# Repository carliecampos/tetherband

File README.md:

# tetherband
Tetherband Board and Schematic Files 

All CAD files and libraries were created using EAGLE CAD. 

The Tetherband repository includes the board and schematic files for: 

A. PC-003 
   This is the prototyping board and has an arduino style pin header for analog control of each subsystem. There is no MCU included. 
B. PC-004
   This is the first completed board and includes the BM832 MCU and a JTAG connector for uploading firmware. The power button was not populated during testing. 
C. Tesseract Library
   This is the library used for all componenets added to PC-003 and PC-003 that were not included in the standard component libraries.

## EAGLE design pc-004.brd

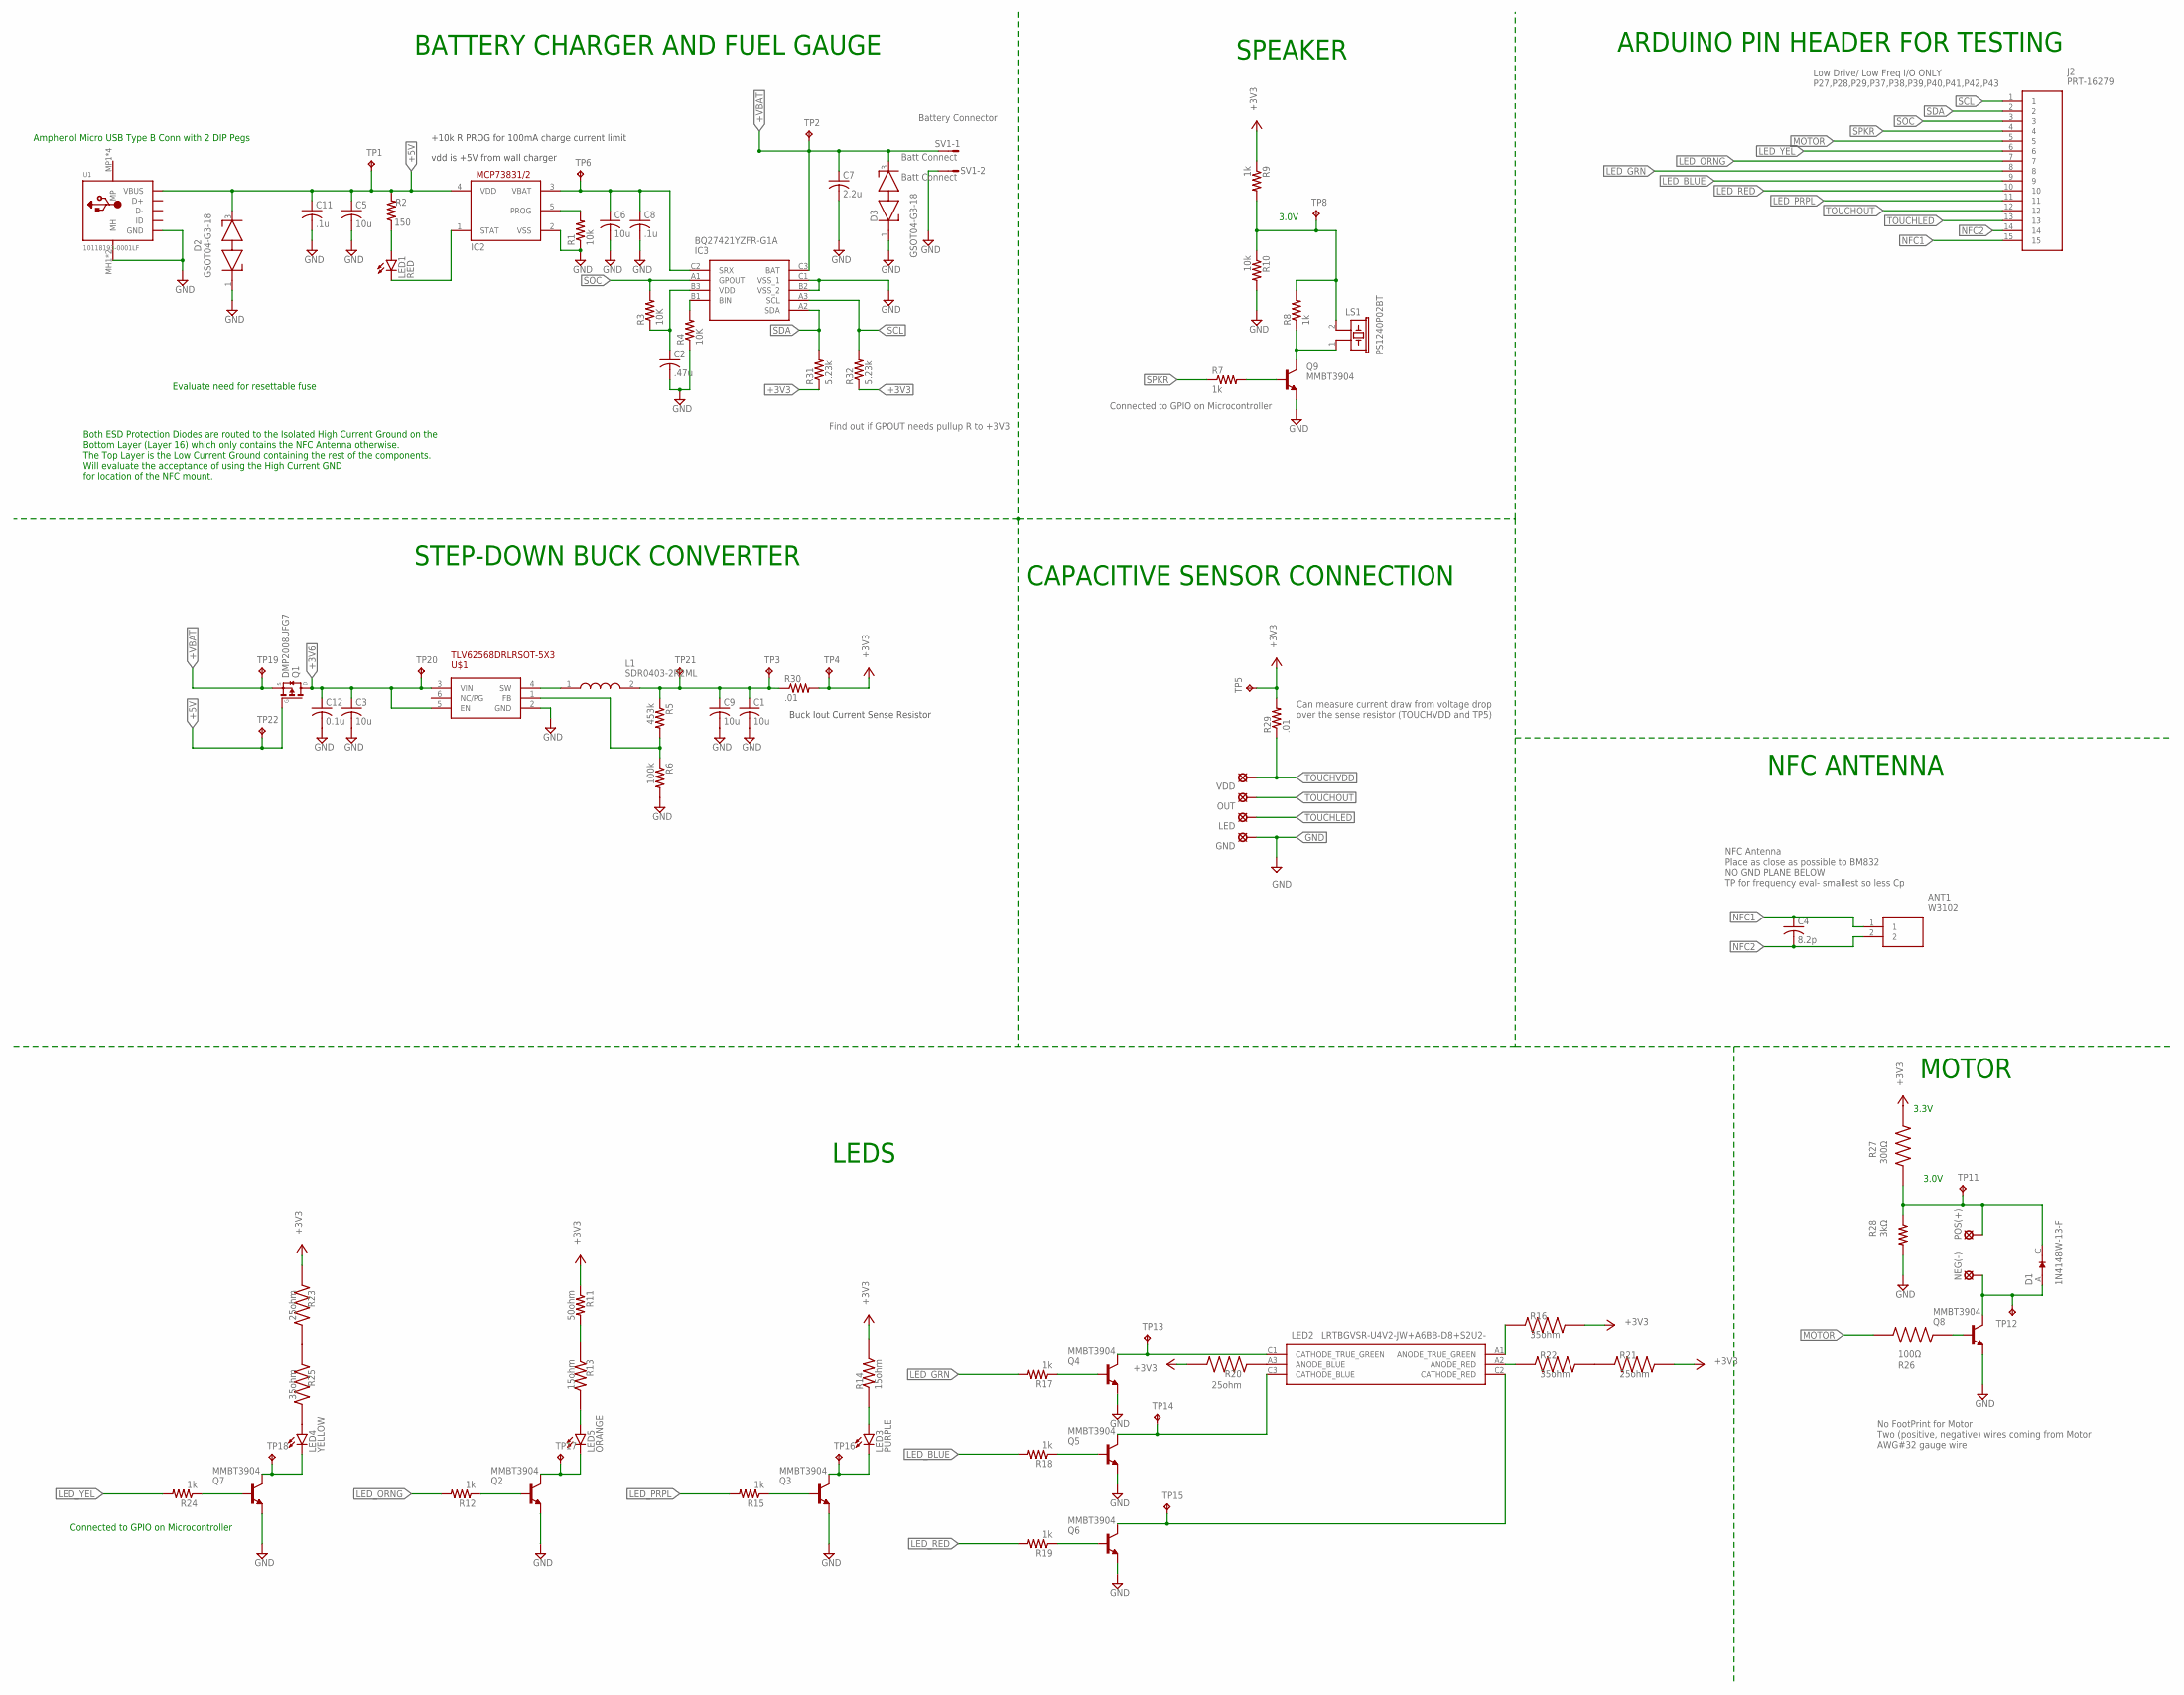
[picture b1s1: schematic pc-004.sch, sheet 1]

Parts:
ANT1: W3102
C1, C3, C5, C6, C9: 10u; CAPC2012X140N
C2: .47u; C0603
C4: 8.2p; C0402K
C7: 2.2u; C0603
C8, C11: .1u; C0603
C12: 0.1u; C0603
D1: 1N4148W-13-F; SOD3715X135N
D2, D3: GSOT04-G3-18; SOT23
GND: LSP10
IC2: MCP73831/OT; SOT23-5L
IC3: BQ27421YZFR-G1A; BGA9C50P3X3_158X162X62
J2: PRT-16279; PRT16279
L1: SDR0403-2R2ML; SDR04032R2ML
LED: LSP10
LED1: RED; LEDC1608X80N
LED2: LRTBGVSR-U4V2-JW+A6BB-D8+S2U2-; LRTBGVSRU4V2JWA6BBD8S2U27Z20S
LED3: PURPLE; LEDC3216X125N
LED4: YELLOW; SML0603
LED5: ORANGE; SML0603
LS1: PS1240P02BT
NEG(-): LSP10
OUT: LSP10
POS(+): LSP10
Q1: DMP2008UFG7
Q2, Q3, Q4, Q5, Q6, Q7, Q8, Q9: MMBT3904; SOT23
R1, R10: 10k; R0402
R2: 150; R0402
R3, R4: 10K; R0402
R5: 453k; R0402
R6: 100k; R0603
R7, R8, R9, R12, R15, R17, R18, R19, R24: 1k; RESC1608X55N
R11: 50ohm; RESC1005X35N
R13, R14: 15ohm; RESC1608X55N
R16, R22, R25: 35ohm; RESC1608X55N
R20, R21, R23: 25ohm; RESC2012X65N
R26: 100Ω; RESC1608X55N
R27: 300Ω; RESC3015X65N
R28: 3kΩ; RESC3216X75N
R29: .01; R0603
R30: .01; RESC3216X68N
R31, R32: 5.23k; R0603
SV1: Batt Connect; L02P
TP1, TP2, TP3, TP4, TP5, TP6, TP8, TP11, TP12, TP13, TP14, TP15, TP16, TP17, TP18, TP19, TP20, TP21, TP22: TESTPOINT; TESTPOINT_PAD-036
U1: 10118193-0001LF; 101181930001LF
U$1: TLV62568DRLRSOT-5X3; SOT50P160X60-6N
VDD: LSP10

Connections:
+3V3: R9.1, R11.1, R14.2, R16.2, R20.2, R21.2, R23.1, R27.1, R29.2, R30.2, R31.1, R32.1, TP4.1, TP5.1; also elsewhere on the board
+3V6: C3.1, C12.1, Q1.5 (D), Q1.6 (D), Q1.7 (D), Q1.8 (D), Q1.9 (D), TP20.1, U$1.3 (VIN), U$1.5 (EN)
+5V: C5.1, C11.1, D2.3 (K2), IC2.4 (VDD), Q1.4 (G), R2.2, TP1.1, TP22.1, U1.1 (VBUS)
+VBAT: C7.1, D3.3 (K2), IC3.C3 (BAT), Q1.1 (S), Q1.2 (S), Q1.3 (S), SV1.1, TP2.1, TP19.1
GND: C1.2, C2.2, C3.2, C5.2, C6.2, C7.2, C8.2, C9.2, C11.2, C12.2, D2.1 (K1), D3.1 (K1), GND.MP, IC2.2 (VSS), IC3.B2 (VSS_2), IC3.C1 (VSS_1), Q2.2 (E), Q3.2 (E), Q4.2 (E), Q5.2 (E), Q6.2 (E), Q7.2 (E), Q8.2 (E), Q9.2 (E), R1.1, R4.1, R6.2, R10.2, R28.2, SV1.2, U1.5 (GND), U1.MH1 (MH), U1.MH2 (MH), U$1.2 (GND); also elsewhere on the board
LED_BLUE: J2.9, R18.2; also elsewhere on the board
LED_GRN: J2.8, R17.2; also elsewhere on the board
LED_ORNG: J2.7, R12.2; also elsewhere on the board
LED_PRPL: J2.11, R15.2; also elsewhere on the board
LED_RED: J2.10, R19.2; also elsewhere on the board
LED_YEL: J2.6, R24.2; also elsewhere on the board
MOTOR: J2.5, R26.1; also elsewhere on the board
unnamed: Q9.1 (B), R7.2
unnamed: LS1.1, Q9.3 (C), R8.1
unnamed: IC2.5 (PROG), R1.2
unnamed: L1.1, U$1.4 (SW)
unnamed: R5.2, R6.1, U$1.1 (FB)
unnamed: IC2.1 (STAT), LED1.1 (C)
unnamed: LED1.2 (A), R2.1
unnamed: Q8.1 (B), R26.2
unnamed: IC3.B1 (BIN), R4.2
unnamed: LS1.2, R8.2, R9.2, R10.1, TP8.1
unnamed: D1.C (K), POS(+).MP, R27.2, R28.1, TP11.1
unnamed: Q2.1 (B), R12.1
unnamed: LED5.C, Q2.3 (C), TP17.1
unnamed: R11.2, R13.1
unnamed: LED5.A, R13.2
unnamed: C1.1, C9.1, L1.2, R5.1, R30.1, TP3.1, TP21.1
unnamed: Q3.1 (B), R15.1
unnamed: LED3.1 (C), Q3.3 (C), TP16.1
unnamed: LED3.2 (A), R14.1
unnamed: R21.1, R22.2
unnamed: Q4.1 (B), R17.1
unnamed: LED2.C1 (CATHODE_TRUE_GREEN), Q4.3 (C), TP13.1
unnamed: D1.A, NEG(-).MP, Q8.3 (C), TP12.1
unnamed: Q5.1 (B), R18.1
unnamed: C6.1, C8.1, IC2.3 (VBAT), IC3.C2 (SRX), TP6.1
unnamed: Q6.1 (B), R19.1
unnamed: LED2.C3 (CATHODE_BLUE), Q5.3 (C), TP14.1
unnamed: LED2.A3 (ANODE_BLUE), R20.1
unnamed: LED2.A1 (ANODE_TRUE_GREEN), R16.1
unnamed: LED2.C2 (CATHODE_RED), Q6.3 (C), TP15.1
unnamed: LED2.A2 (ANODE_RED), R22.1
unnamed: Q7.1 (B), R24.1
unnamed: LED4.C, Q7.3 (C), TP18.1
unnamed: LED4.A, R25.2
unnamed: R23.2, R25.1
unnamed: C2.1, IC3.B3 (VDD), R3.1
NFC1: ANT1.1, C4.1, J2.15; also elsewhere on the board
NFC2: ANT1.2, C4.2, J2.14; also elsewhere on the board
SCL: IC3.A3 (SCL), J2.1, R32.2; also elsewhere on the board
SDA: IC3.A2 (SDA), J2.2, R31.2; also elsewhere on the board
SOC: IC3.A1 (GPOUT), J2.3, R3.2; also elsewhere on the board
SPKR: J2.4, R7.1; also elsewhere on the board
TOUCHLED: J2.13, LED.MP
TOUCHOUT: J2.12, OUT.MP; also elsewhere on the board
TOUCHVDD: R29.1, VDD.MP

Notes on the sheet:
NFC Antenna Place as close as possible to BM832 NO GND PLANE BELOW TP for frequency eval- smallest so less Cp
vdd is +5V from wall charger
+10k R PROG for 100mA charge current limit
Battery Connector
Low Drive/ Low Freq I/O ONLY P27,P28,P29,P37,P38,P39,P40,P41,P42,P43
Connected to GPIO on Microcontroller
3.0V
3.3V
No FootPrint for Motor Two (positive, negative) wires coming from Motor AWG#32 gauge wire
Evaluate need for resettable fuse
Buck Iout Current Sense Resistor
NFC ANTENNA
CAPACITIVE SENSOR CONNECTION
SPEAKER
BATTERY CHARGER AND FUEL GAUGE
STEP-DOWN BUCK CONVERTER
LEDS
MOTOR
ARDUINO PIN HEADER FOR TESTING
Find out if GPOUT needs pullup R to +3V3
Can measure current draw from voltage drop over the sense resistor (TOUCHVDD and TP5)
Amphenol Micro USB Type B Conn with 2 DIP Pegs
Both ESD Protection Diodes are routed to the Isolated High Current Ground on the Bottom Layer (Layer 16) which only contains the NFC Antenna otherwise. The Top Layer is the Low Current Ground containing the rest of the components. Will evaluate the acceptance of using the High Current GND for locat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

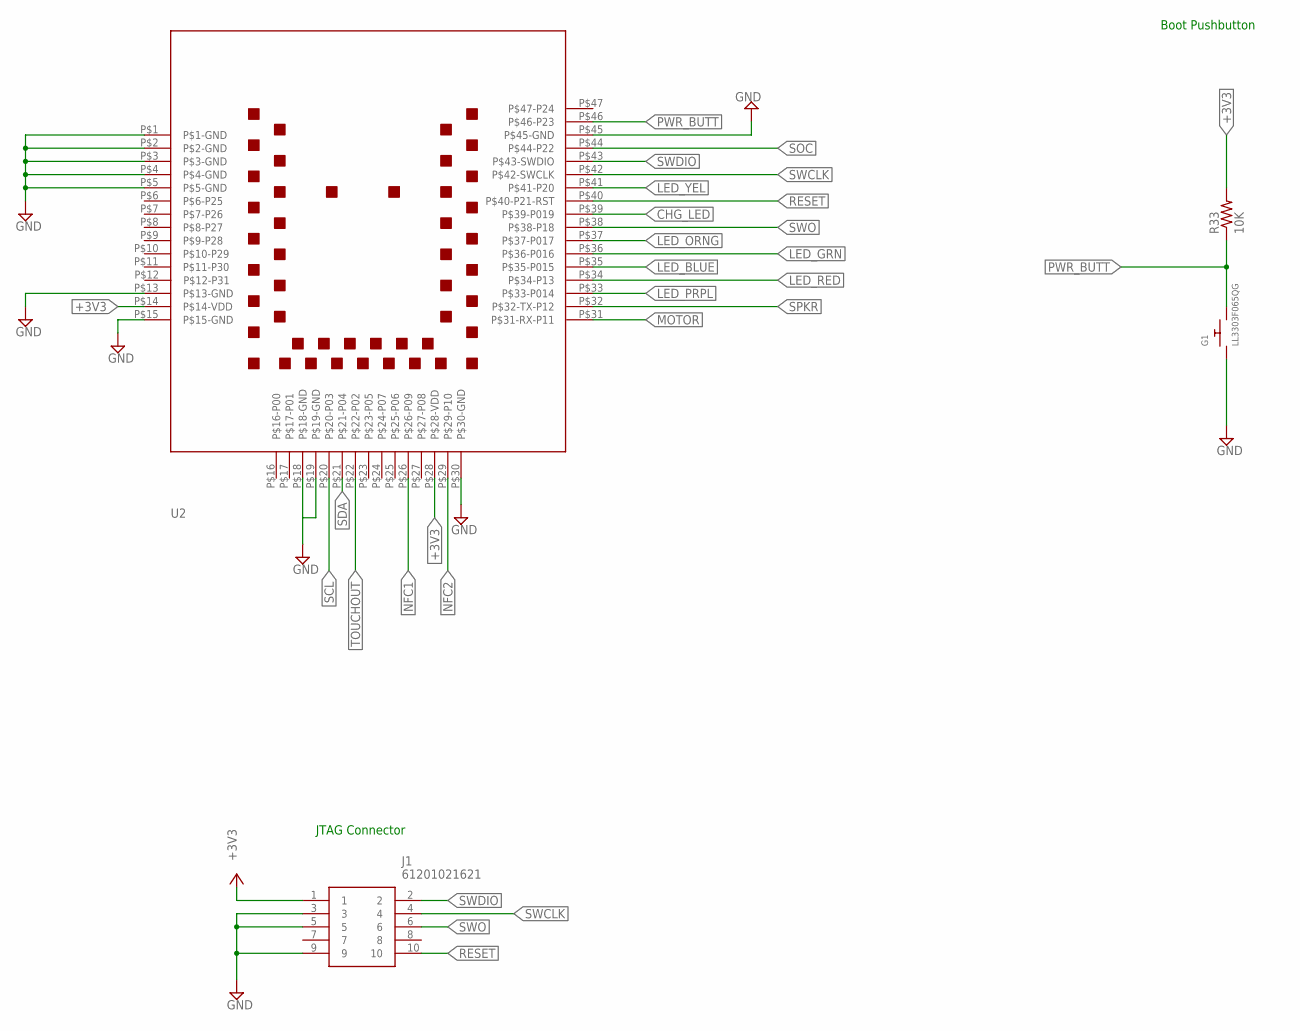
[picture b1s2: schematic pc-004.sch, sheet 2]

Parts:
G1: LL3303F065QG
J1: 61201021621; SHDR10W64P254_2X5_2036X885X925
R33: 10K; R0402
U2: BM832

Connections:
+3V3: J1.1, R33.2, U2.P$14 (P$14-VDD), U2.P$28 (P$28-VDD); also elsewhere on the board
CHG_LED: U2.P$39 (P$39-P019)
GND: G1.P$1, G1.P$2, J1.3, J1.5, J1.9, U2.P$1 (P$1-GND), U2.P$2 (P$2-GND), U2.P$3 (P$3-GND), U2.P$4 (P$4-GND), U2.P$5 (P$5-GND), U2.P$13 (P$13-GND), U2.P$15 (P$15-GND), U2.P$18 (P$18-GND), U2.P$19 (P$19-GND), U2.P$30 (P$30-GND), U2.P$45 (P$45-GND); also elsewhere on the board
LED_BLUE: U2.P$35 (P$35-P015); also elsewhere on the board
LED_GRN: U2.P$36 (P$36-P016); also elsewhere on the board
LED_ORNG: U2.P$37 (P$37-P017); also elsewhere on the board
LED_PRPL: U2.P$33 (P$33-P014); also elsewhere on the board
LED_RED: U2.P$34 (P$34-P13); also elsewhere on the board
LED_YEL: U2.P$41 (P$41-P20); also elsewhere on the board
MOTOR: U2.P$31 (P$31-RX-P11); also elsewhere on the board
NFC1: U2.P$26 (P$26-P09); also elsewhere on the board
NFC2: U2.P$29 (P$29-P10); also elsewhere on the board
PWR_BUTT: G1.P$3, G1.P$4, R33.1, U2.P$46 (P$46-P23)
RESET: J1.10, U2.P$40 (P$40-P21-RST)
SCL: U2.P$20 (P$20-P03); also elsewhere on the board
SDA: U2.P$21 (P$21-P04); also elsewhere on the board
SOC: U2.P$44 (P$44-P22); also elsewhere on the board
SPKR: U2.P$32 (P$32-TX-P12); also elsewhere on the board
SWCLK: J1.4, U2.P$42 (P$42-SWCLK)
SWDIO: J1.2, U2.P$43 (P$43-SWDIO)
SWO: J1.6, U2.P$38 (P$38-P18)
TOUCHOUT: U2.P$22 (P$22-P02); also elsewhere on the board

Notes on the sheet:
Boot Pushbutton
JTAG Connector

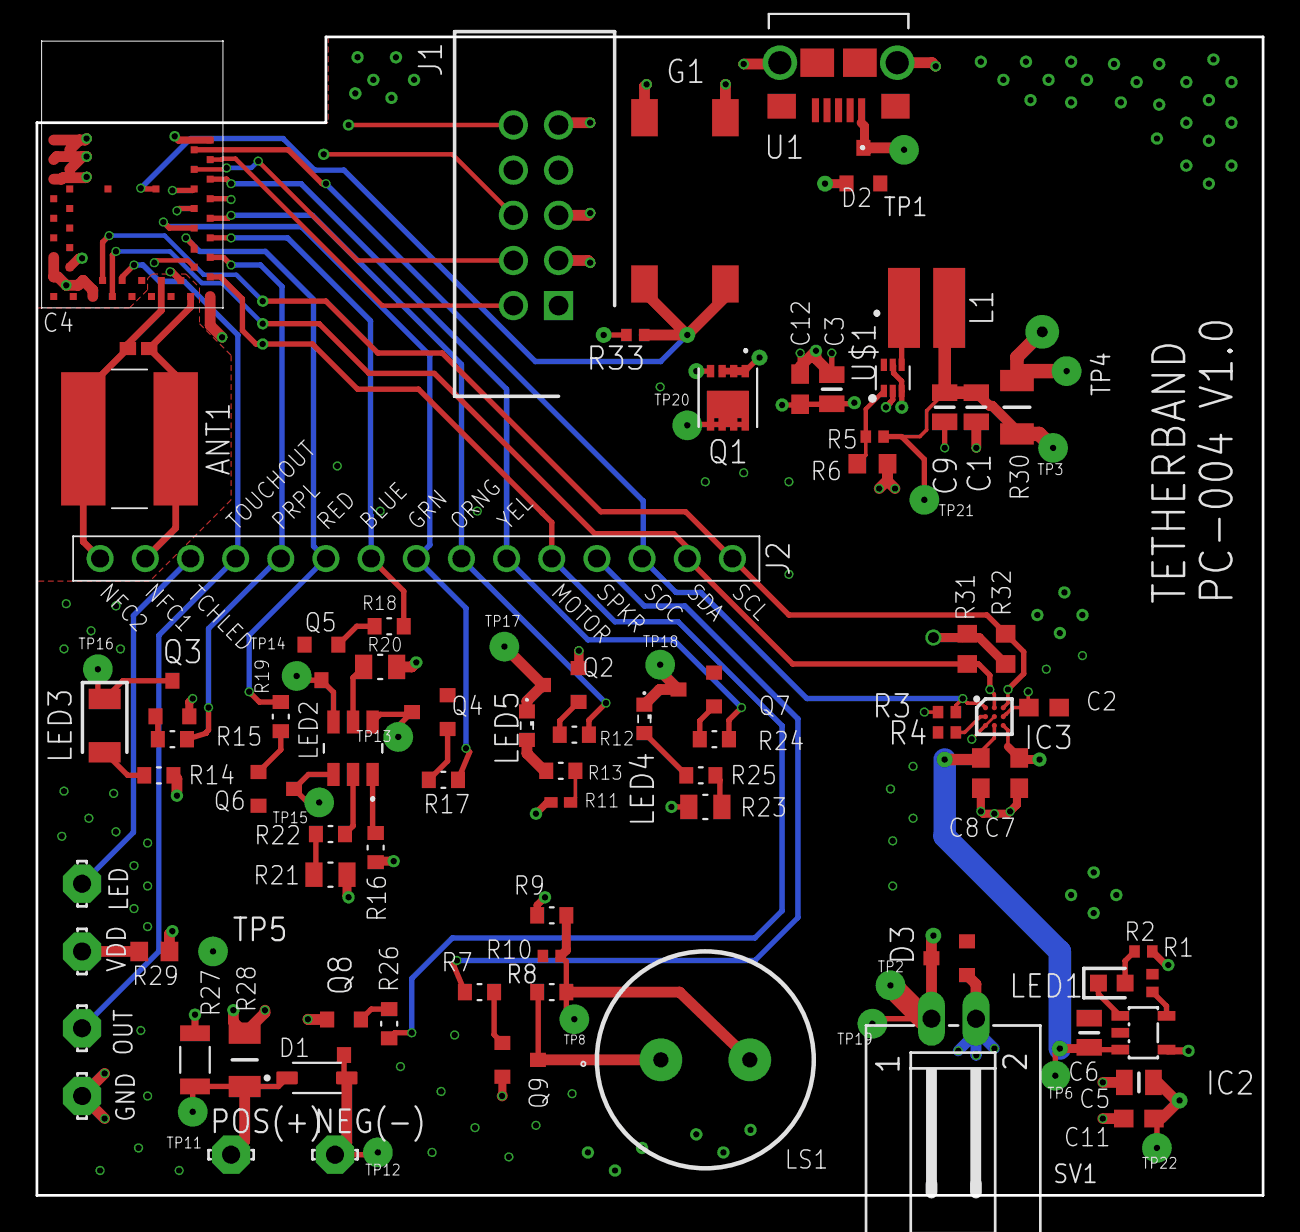
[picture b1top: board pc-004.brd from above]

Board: 4 copper layers, 69.0 x 65.2 mm, 98 parts (0 on the bottom side), 62 nets.

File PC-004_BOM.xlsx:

Obtained | Qty | Value | Device | Package | Parts | Description | Column1 | _1
Y | 1 |  | BM832 | BM832 | U2
Y | 1 | .01 | PCS1206DR0100ET | RESC3216X68N | R30 | Current Sense Resistors - SMD 1W 0.010 OHMS 0.5%
Y | 1 | .01 | R-US_R0603 | R0603 | R29 | RESISTOR, American symbol
Y | 2 | .1u | C-USC0603 | C0603 | C8, C11 | CAPACITOR, American symbol
Y | 1 | .47u | C-USC0603 | C0603 | C2 | CAPACITOR, American symbol
Y | 1 | 0.1u | C-USC0603 | C0603 | C12 | CAPACITOR, American symbol
Y | 1 | 100k | R-US_R0603 | R0603 | R6 | RESISTOR, American symbol
Y | 1 | 100Ω | SR0603FR-7T100RL | RESC1608X55N | R26 | Check prices
Y | 1 | 10118193-0001LF - micro USB | 10118193-0001LF | 101181930001LF | U1
Y | 3 | 10K | R-US_R0402 | R0402 | R3, R4, R33 | RESISTOR, American symbol
Y | 2 | 10k | R-US_R0402 | R0402 | R1, R10 | RESISTOR, American symbol
Y | 5 | 10u | CL21A106KOQNNNE | CAPC2012X140N | C1, C3, C5, C6, C9
Y | 1 | 150 | R-US_R0402 | R0402 | R2 | RESISTOR, American symbol
Y | 2 | 15ohm | SR0603JR-0715RL | RESC1608X55N | R13, R14 | Check prices
Y | 1 | 1N4148W-13-F | 1N4148W-13-F | SOD3715X135N | D1 | 1N4148W Series 2 A 100 V 400 mW Surface Mount Fast Switching Diode - SOD-123 Ch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
Y | 9 | 1k | CRCW06031K00FKEAC | RESC1608X55N | R7, R8, R9, R12, R15, R17, R18, R19, R24
Y | 1 | 2.2u | C-USC0603 | C0603 | C7 | CAPACITOR, American symbol
Y | 3 | 25ohm | RQ73C2A25R5BTD | RESC2012X65N | R20, R21, R23 | Check prices
Y | 1 | 300Ω | CRCW1206300RFKEAC | RESC3015X65N | R27 | Check prices
Y | 3 | 35ohm | RT0603BRD0735R2L | RESC1608X55N | R16, R22, R25
Y | 1 | 3kΩ | CR1206-FX-3001ELF | RESC3216X75N | R28
Y | 1 | 453k | R-US_R0402 | R0402 | R5 | RESISTOR, American symbol
Y | 2 | 5.23k | R-US_R0603 | R0603 | R31, R32 | RESISTOR, American symbol
Y | 1 | 50ohm | RT0402BRE0750RL | RESC1005X35N | R11
 | 1 | 61201021621 | 61201021621 | SHDR10W64P254_2X5_2036X885X925 | J1 | 10 way 2.54mm male box Header Wurth Elektronik 612 Series, 2.54mm Pitch 10 Way 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
Y | 1 | 8.2p | C-USC0402K | C0402K | C4 | CAPACITOR, American symbol
N - only 1 | 1 | BQ27421YZFR-G1A | BQ27421YZFR-G1A | BGA9C50P3X3_158X162X62 | IC3
N/A | 1 | Batt Connect | L02P | L02P | SV1 | AMP MT CONNECTOR
Y | 1 | DMP2008UFG7 | DMP2008UFG | DMP2008UFG7 | Q1
Y | 2 | GSOT04-G3-18 | GSOT04-G3-18 | SOT23 | D2, D3
 | 1 | LL3303F065QG | LL3303F065QG | LL3303F065QG | G1
Y | 1 | LRTBGVSR-U4V2-JW+A6BB-D8+S2U2- | LRTBGVSR-U4V2-JW+A6BB-D8+S2U2- | LRTBGVSRU4V2JWA6BBD8S2U27Z20S | LED2 | Standard LEDs - SMD RGB LED OSIRE E3635
N/A | 6 | LSP10 | LSP10 | LSP10 | GND, LED, NEG(-), OUT, POS(+), VDD | SOLDER PAD drill 1.0 mm, distributor Buerklin, 12H555
N - only 3 | 1 | MCP73831/OT | MCP73831/OT | SOT23-5L | IC2 | MCP73831/2
Y | 8 | MMBT3904 | MMBT3904-7-FNSMD | SOT23 | Q2, Q3, Q4, Q5, Q6, Q7, Q8, Q9
Y | 1 | ORANGE | SML-D15YWT86CORANGE | SML0603 | LED5
 | 1 | PRT-16279 | PRT-16279 | PRT16279 | J2 | ARDUINO NANO STACKABLE HEADERS
Y | 1 | PS1240P02BT Speaker | PS1240P02BT | PS1240P02BT | LS1 | Audio Indicators & Alerts Round 12.2mmx6.5mm 4kHz Vin=3V
Y | 1 | PURPLE | APTR3216-VFX | LEDC3216X125N | LED3
Y | 1 | RED | 150060RS75000 | LEDC1608X80N | LED1
 | 1 | SDR0403-2R2ML | SDR0403-2R2ML | SDR04032R2ML | L1 | Bourns SDR0403 Series Type SMD Wire-wound SMD Inductor with a Ferrite DR Core, 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
N/A | 19 | TESTPOINT | TESTPOINT | TESTPOINT_PAD-036 | TP1, TP2, TP3, TP4, TP5, TP6, TP8, TP11, TP12, TP13, TP14, TP15, TP16, TP17, TP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
Y | 1 | TLV62568DRLRSOT-5X3 | TLV62568DRLRSOT-5X3 | SOT50P160X60-6N | U$1
Y | 1 | W3102 | W3102 | W3102 | ANT1 | Antennas Ant Embedded NFC 13.56MHz
Y | 1 | YELLOW | SML-D15YWT86CYELLOW | SML0603 | LED4
Y | 1 | MMBT222A BJT Transistor | MMBT2222A-AU_R1_000A1 |  | ?
